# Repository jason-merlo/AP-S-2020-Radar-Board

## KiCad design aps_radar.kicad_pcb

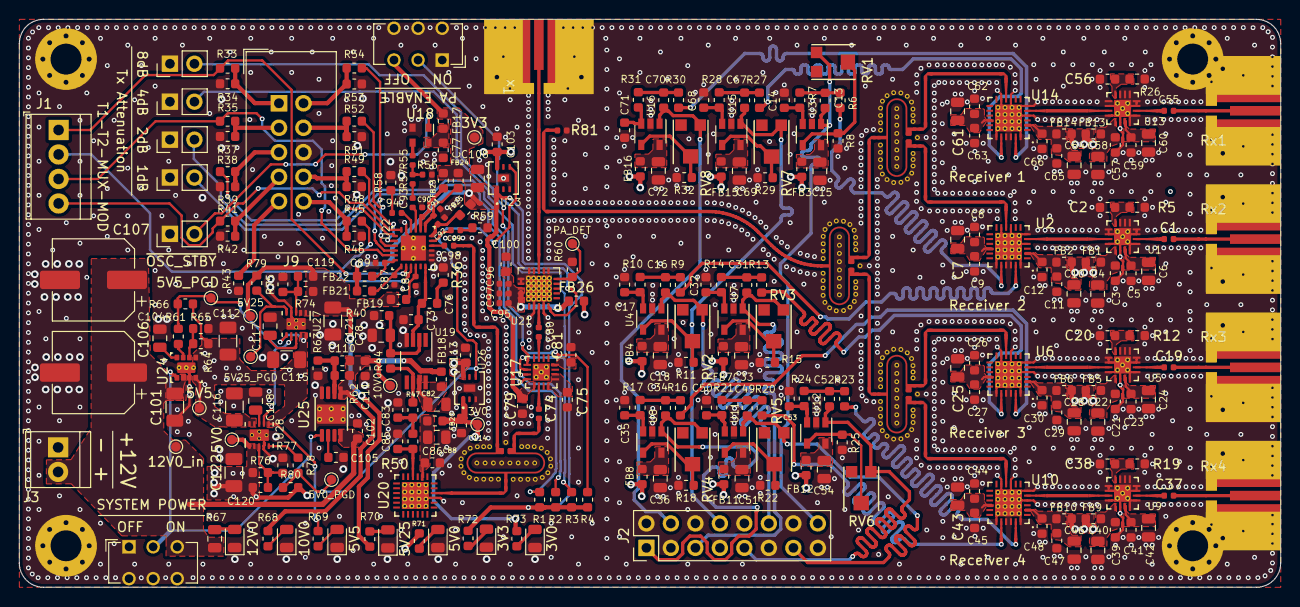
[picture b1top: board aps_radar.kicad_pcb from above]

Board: 4 copper layers, 130.8 x 58.9 mm, 360 parts (0 on the bottom side), 217 nets.

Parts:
C1, C19, C37, C55: 1.2pF; C_0402_1005Metric
C2, C20, C38, C56, C86, C105, C110, C119, C120: 10nF; C_0603_1608Metric
C3, C5, C21, C23, C39, C41, C57, C59: 1000pF; C_0603_1608Metric
C4, C6, C15, C18, C22, C24, C33, C36, C40, C42, C51, C54, C58, C60, C69, C72, C78, C82, C117, C118: 0.1uF; C_0805_2012Metric
C7, C10, C25, C28, C43, C46, C61, C64, C88, C108: 4.7uF; C_0805_2012Metric
C8, C11, C26, C29, C44, C47, C62, C65: 100pF; C_0603_1608Metric
C9, C12, C13, C14, C16, C17, C27, C30, C31, C32, C34, C35, C45, C48, C49, C50, C52, C53, C63, C66, C67, C68, C70, C71, C77: 0.01uF; C_0603_1608Metric
C73: 68pF; C_0603_1608Metric
C74, C80, C93, C94, C98, C99: 10pF; C_0402_1005Metric
C75, C81: 330pF; C_0603_1608Metric
C76: 0.68nF; C_0603_1608Metric
C79, C83: 1.8nF; C_0603_1608Metric
C84, C87, C89: 100pF; C_0402_1005Metric
C85: 0.82nF; C_0603_1608Metric
C90, C91, C92, C95, C96, C97: 0.1uF; C_0402_1005Metric
C100: 10uF; C_0603_1608Metric
C101, C112, C115, C116, C121, C122: 10uF; C_1206_3216Metric
C102, C111: 2.2uF; C_0603_1608Metric
C103, C113, C114: 1uF; C_0603_1608Metric
C104: 4.3nF; C_0805_2012Metric
C106: 68uF; CP_Elec_8x11.9
C107: DNP; CP_Elec_8x11.9
D1: 12V0; D_0805_2012Metric
D2: 10V0; D_0805_2012Metric
D3: 5V5; D_0805_2012Metric
D4: 5V25; D_0805_2012Metric
D5: 5V0; D_0805_2012Metric
D6: 3V3; D_0805_2012Metric
D7: 3V0; D_0805_2012Metric
FB1, FB2, FB3, FB4, FB5, FB6, FB7, FB8, FB9, FB10, FB11, FB12, FB13, FB14, FB15, FB16, FB17, FB18, FB20, FB26: 0; L_0603_1608Metric
FB19, FB21, FB22, FB23, FB24, FB25: 120 ohm; L_0603_1608Metric
H1, H2, H3, H4: MountingHole; MountingHole_3.2mm_M3_Pad_Via
J1: TRIG_MUX_OUT; TerminalBlock_TE_282834-4_1x04_P2.54mm_Horizontal
J2: IF_OUT; PinHeader_2x08_P2.54mm_Vertical
J3: POWER_IN; TerminalBlock_TE_282834-2_1x02_P2.54mm_Horizontal
J4: Tx; SMA_Molex_Transition
J5: Rx1; SMA_Molex_Transition
J6: Rx2; SMA_Molex_Transition
J7: Rx3; SMA_Molex_Transition
J8: Rx4; SMA_Molex_Transition
J9: LMX2491_CONN; IDC-Header_2x05_P2.54mm_Vertical
JP1: 1dB; PinHeader_1x02_P2.54mm_Vertical
JP2: 2dB; PinHeader_1x02_P2.54mm_Vertical
JP3: 4dB; PinHeader_1x02_P2.54mm_Vertical
JP4: 8dB; PinHeader_1x02_P2.54mm_Vertical
JP5: ~OSC_STBY; PinHeader_1x02_P2.54mm_Vertical
R1, R2, R3, R4, R33, R34, R35, R37, R38, R39, R41, R42, R45, R46, R48, R49, R51, R52, R53, R54, R60, R63: 10k; R_0603_1608Metric
R5, R12, R19, R26: 825; R_0603_1608Metric
R6, R7, R8, R9, R10, R11, R13, R14, R15, R16, R17, R18, R20, R21, R22, R23, R24, R25, R27, R28, R29, R30, R31, R32, R68: 499; R_0603_1608Metric
R36: 1.2k; R_0603_1608Metric
R40: 1.0k; R_0603_1608Metric
R43: DNP; R_0603_1608Metric
R44: 1.24k; R_0603_1608Metric
R47: 8.2; R_0603_1608Metric
R50: 22; R_0603_1608Metric
R55, R57: 18; R_0402_1005Metric
R56: 68; R_0402_1005Metric
R58, R59: 51; R_0603_1608Metric
R61, R78: 0; R_0603_1608Metric
R62: 86.6k; R_0603_1608Metric
R64: 590k; R_0603_1608Metric
R65, R66, R79, R80: 100k; R_0603_1608Metric
R67: 649; R_0805_2012Metric
R69: 274; R_0603_1608Metric
R70: 261; R_0603_1608Metric
R71: 249; R_0603_1608Metric
R72: 165; R_0603_1608Metric
R73: 150; R_0603_1608Metric
R74, R76: 332k; R_0603_1608Metric
R75: 59.7k; R_0603_1608Metric
R77: 63.4k; R_0603_1608Metric
R81: 50; R_0402_1005Metric
RV1, RV2, RV3, RV4, RV5, RV6, RV7, RV8: 50k; Bourns_Trimpot_TC33
SW1: PA_EN; SW_CuK_JS202011AQN_DPDT_Angled
SW2: ON/OFF; SW_CuK_JS202011AQN_DPDT_Angled
TL1: coupled_line_14db
TL2, TL3, TL4, TL5: wilkinson_3dB; wilkinson_3db
TL6, TL7, TL8, TL9, TL16, TL17, TL18, TL19, TL20, TL21, TL47, TL48, TL49, TL50, TL51, TL52, TL53, TL54, TL55, TL56, TL57, TL58: mitered_bend; mitered_bend_50
TL10, TL11, TL23, TL24, TL25, TL26, TL27, TL28, TL29, TL30, TL31, TL32, TL33, TL34, TL35, TL36, TL37, TL38, TL39, TL40, TL41, TL42, TL43, TL44, TL45, TL46: ic_taper; IC_Taper_0.22_0.35
TL12, TL13, TL14, TL15, TL22: ic_taper; IC_Taper_0.25_0.35
TP1: PA_DET; TestPoint_Pad_D1.0mm
TP2: 3V3; TestPoint_Pad_D1.0mm
TP3: 12V0_in; TestPoint_Pad_D1.0mm
TP4: 10V0; TestPoint_Pad_D1.0mm
TP5: 5V5; TestPoint_Pad_D1.0mm
TP6: 5V5_PGD; TestPoint_Pad_D1.0mm
TP7: 3V0; TestPoint_Pad_D1.0mm
TP8: 5V25; TestPoint_Pad_D1.0mm
TP9: 5V25_PGD; TestPoint_Pad_D1.0mm
TP10: 5V0; TestPoint_Pad_D1.0mm
TP11: 5V0_PGD; TestPoint_Pad_D1.0mm
U1, U5, U9, U13: HMC717A; HMC-LP3
U2, U6, U10, U14: HMC951A; HMC-LP4
U3, U4, U7, U8, U11, U12, U15, U16: OPA192; SOT-23-5
U17: HMC540S; HMC-LP3
U18: ASDMB-100MHz; Oscillator_SMD_Abracon_ASDMB-4Pin_2.5x2.0mm
U19: OPA192; VSSOP-8_3.0x3.0mm_P0.65mm
U20: HMC431; HMC-LP4
U21: TQP5523; QFN4-20-TQP5523
U22: LMX2491RTWR
U23: LP5900-TL3.3; LP5900_NGF_6
U24: TPS82140; TPS82140SILR
U25: TPS7A49; TPS7A4901_DGN_8
U26: LP5900-TL3.0; LP5900_NGF_6
U27: TPS7A90; TPS7A9xDSKR
U28: TPS7A92; TPS7A9xDSKR

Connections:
+3V0: C114.1, FB20.2, R73.2, TP7.1, U26.1
+3V3: C79.1, C108.1, FB17.1, FB21.2, FB22.2, FB23.2, FB24.2, FB25.2, R1.1, R2.1, R3.1, R4.1, R72.2, SW1.3, TP2.1, U17.1, U23.1
+5V: C103.1, C113.1, C120.1, C122.1, FB1.1, FB2.1, FB3.1, FB4.1, FB5.1, FB6.1, FB7.1, FB8.1, FB9.1, FB10.1, FB11.1, FB12.1, FB13.1, FB14.1, FB15.1, FB16.1, FB26.2, R71.2, R76.1, R80.1, TP10.1, U23.6, U26.6, U28.1, U28.2
+5V25: C119.1, C121.1, FB19.2, R70.2, R74.1, R79.1, TP8.1, U27.1, U27.2
+10V: C110.1, C111.1, FB18.2, R62.1, R68.2, TP4.1, U25.1
/LMX_MOD: J1.4, R41.2, U22.12
/LMX_MUXOUT: J1.3, R35.2, U22.17
/LMX_TRIG1: J1.1, R33.2, U22.20
/LMX_TRIG2: J1.2, R45.2, U22.21
/RX1_I: C70.1, J2.4, RV8.1, U16.1
/RX1_Q: C67.1, J2.8, RV7.1, U15.1
/RX2_I: C16.1, J2.12, RV2.1, U4.1
/RX2_Q: C13.1, J2.16, RV1.1, U3.1
/RX3_I: C34.1, J2.1, RV4.1, U8.1
/RX3_Q: C31.1, J2.5, RV3.1, U7.1
/RX4_I: C52.1, J2.9, RV6.1, U12.1
/RX4_Q: C49.1, J2.13, RV5.1, U11.1
/power/5V0_PGD: R78.1, R80.2, TP11.1, U23.4, U26.4
/power/5V5_OUT: C112.1, C115.1, C116.1, R64.1, R66.1, R69.2, TP5.1, U24.4, U24.5, U27.6, U27.9, U27.10, U28.6, U28.9, U28.10
/power/5V5_PGD: R61.1, R66.2, TP6.1, U27.7, U28.7
/power/5V25_PGD: R79.2, TP9.1, U27.5
/power/+12V0_IN_CONN: C101.1, C102.1, C106.1, C107.1, J3.2, R67.2, SW2.3, TP3.1, U24.2, U25.8
/power/POWER_SW: SW2.2, U24.1, U25.5
/receiver_1/ANT_IN: C55.2, J5.1
/receiver_1/IF1_RAW: R30.2, TL45.2
/receiver_1/IF2_RAW: R27.2, TL46.2
/receiver_1/LNA_OUT: TL32.2, TL36.2
/receiver_2/ANT_IN: C1.2, J6.1
/receiver_2/IF1_RAW: R9.2, TL24.2
/receiver_2/IF2_RAW: R6.2, TL37.2
/receiver_2/LNA_OUT: TL29.2, TL33.2
/receiver_3/ANT_IN: C19.2, J7.1
/receiver_3/IF1_RAW: R16.2, TL39.2
/receiver_3/IF2_RAW: R13.2, TL40.2
/receiver_3/LNA_OUT: TL30.2, TL34.2
/receiver_4/ANT_IN: C37.2, J8.1
/receiver_4/IF1_RAW: R23.2, TL42.2
/receiver_4/IF2_RAW: R20.2, TL43.2
/receiver_4/LNA_OUT: TL31.2, TL35.2
/transmitter/ATTEN_OUT: C80.2, TL14.2
/transmitter/LMX_CE: R38.2, U22.13
/transmitter/LMX_CLK: R49.2, U22.14
/transmitter/LMX_CPOUT: C73.1, C76.1, TL22.2, U19.3
/transmitter/LMX_DATA: R52.2, U22.15
/transmitter/LMX_FIN: C98.1, TL19.1
/transmitter/LMX_LE: R54.2, U22.16
/transmitter/LMX_VCP: C84.1, FB19.1, U22.22
/transmitter/LO_1: TL50.1, TL55.2
/transmitter/LO_2: TL47.1, TL57.1
/transmitter/LO_3: TL48.1, TL56.2
/transmitter/LO_4: TL49.1, TL58.1
/transmitter/PA_OUT: TL1.1, TL15.2
/transmitter/REF_OUT: R55.2, U18.3
/transmitter/TX_OUT: J4.1, TL1.2
/transmitter/VCO_OUT: C74.1, TL21.1
/~ATTEN_1DB: JP1.2, R1.2, U17.16
/~ATTEN_2DB: JP2.2, R2.2, U17.15
/~ATTEN_4DB: JP3.2, R3.2, U17.14
/~ATTEN_8DB: JP4.2, R4.2, U17.13
GND: C2.2, C3.2, C4.2, C5.2, C6.2, C7.2, C8.1, C9.1, C10.2, C11.1, C12.1, C14.2, C15.2, C17.2, C18.2, C20.2, C21.2, C22.2, C23.2, C24.2, C25.2, C26.1, C27.1, C28.2, C29.1, C30.1, C32.2, C33.2, C35.2, C36.2, C38.2, C39.2, C40.2, C41.2, C42.2, C43.2, C44.1, C45.1, C46.2, C47.1, C48.1, C50.2, C51.2, C53.2, C54.2, C56.2, C57.2, C58.2, C59.2, C60.2, C61.2, C62.1, C63.1, C64.2, C65.1, C66.1, C68.2, C69.2, C71.2, C72.2, C73.2, C75.1, C77.2, C78.2, C79.2, C81.2, C82.2, C83.2, C84.2, C85.2, C86.2, C87.2, C88.2, C89.2, C90.2, C91.2, C92.2, C95.2, C96.2, C97.2, C100.2, C101.2, C102.2, C103.2, C104.2, C105.2, C106.2, C107.2, C108.2, C111.2, C112.2, C113.2, C114.2, C115.2, C116.2, C117.2, C118.2, C121.2, C122.2, D1.1, D2.1, D3.1, D4.1, D5.1, D6.1, D7.1, H1.1, H2.1, H3.1, H4.1, J2.2, J2.3, J2.6, J2.7, J2.10, J2.11, J2.14, J2.15, J3.1, J4.2, J5.2, J6.2, J7.2, J8.2, J9.6, JP1.1, JP2.1, JP3.1, JP4.1, JP5.1, R5.1, R8.2, R11.2, R12.1, R15.2, R18.2, R19.1, R22.2, R25.2, R26.1, R29.2, R32.2, R34.1, R36.2, R37.1, R39.1, R40.2, R42.1, R43.1, R46.1, R48.1, R51.1, R53.1, R56.2, R58.1, R59.1, R60.2, R63.2, R65.2, R75.2, R77.2, R81.2, SW1.1, SW1.4, SW1.5, SW1.6, SW2.1, SW2.4, SW2.5, SW2.6, TL2.5, TL3.5, TL4.5, TL5.5, U1.1, U1.3, U1.4, U1.5, U1.6, U1.7, U1.9, U1.10, U1.12, U1.14, U1.16, U1.17, U2.4, U2.6, U2.9, U2.11, U2.19, U2.21, U2.22, U2.24, U2.25, U3.2, U4.2, U5.1, U5.3, U5.4, U5.5, U5.6, U5.7, U5.9, U5.10, U5.12, U5.14, U5.16, U5.17, U6.4, U6.6, U6.9, U6.11, U6.19, U6.21, U6.22, U6.24, U6.25, U7.2, U8.2, U9.1, U9.3, U9.4, U9.5, U9.6, U9.7, U9.9, U9.10, U9.12, U9.14, U9.16, U9.17, U10.4, U10.6, U10.9, U10.11, U10.19, U10.21, U10.22, U10.24, U10.25, U11.2, U12.2, U13.1, U13.3, U13.4, U13.5, U13.6, U13.7, U13.9, U13.10, U13.12, U13.14, U13.16, U13.17, U14.4, U14.6, U14.9, U14.11, U14.19, U14.21, U14.22, U14.24, U14.25, U15.2, U16.2, U17.17, U18.2, U19.4, U20.15, U20.25, U21.2, U21.4, U21.11, U21.12, U21.14, U21.15, U21.16, U21.17, U21.21, U22.1, U22.2, U22.3, U22.11, U22.25, U23.3, U23.7, U24.3, U24.9, U25.4, U25.9, U26.3, U26.7, U27.4, U27.11, U28.4, U28.11
unnamed: C1.1, TL25.2
unnamed: C2.1, R5.2, U1.8
unnamed: C3.1, C4.1, C5.1, C6.1, FB1.2, U1.13, U1.15
unnamed: C7.1, C8.2, C9.2, C10.1, C11.2, C12.2, FB2.2, U2.2, U2.16
unnamed: C13.2, R6.1, R7.2
unnamed: C14.1, R7.1, U3.3
unnamed: C15.1, FB3.2, U3.5
unnamed: C16.2, R9.1, R10.2
unnamed: C17.1, R10.1, U4.3
unnamed: C18.1, FB4.2, U4.5
unnamed: C19.1, TL26.2
unnamed: C20.1, R12.2, U5.8
unnamed: C21.1, C22.1, C23.1, C24.1, FB5.2, U5.13, U5.15
unnamed: C25.1, C26.2, C27.2, C28.1, C29.2, C30.2, FB6.2, U6.2, U6.16
unnamed: C31.2, R13.1, R14.2
unnamed: C32.1, R14.1, U7.3
unnamed: C33.1, FB7.2, U7.5
unnamed: C34.2, R16.1, R17.2
unnamed: C35.1, R17.1, U8.3
unnamed: C36.1, FB8.2, U8.5
unnamed: C37.1, TL27.2
unnamed: C38.1, R19.2, U9.8
unnamed: C39.1, C40.1, C41.1, C42.1, FB9.2, U9.13, U9.15
unnamed: C43.1, C44.2, C45.2, C46.1, C47.2, C48.2, FB10.2, U10.2, U10.16
unnamed: C49.2, R20.1, R21.2
unnamed: C50.1, R21.1, U11.3
unnamed: C51.1, FB11.2, U11.5
unnamed: C52.2, R23.1, R24.2
unnamed: C53.1, R24.1, U12.3
unnamed: C54.1, FB12.2, U12.5
unnamed: C55.1, TL28.2
unnamed: C56.1, R26.2, U13.8
unnamed: C57.1, C58.1, C59.1, C60.1, FB13.2, U13.13, U13.15
unnamed: C61.1, C62.2, C63.2, C64.1, C65.2, C66.2, FB14.2, U14.2, U14.16
unnamed: C67.2, R27.1, R28.2
unnamed: C68.1, R28.1, U15.3
unnamed: C69.1, FB15.2, U15.5
unnamed: C70.2, R30.1, R31.2
unnamed: C71.1, R31.1, U16.3
unnamed: C72.1, FB16.2, U16.5
unnamed: C74.2, TL10.2
unnamed: C75.2, U17.4, U17.5, U17.6
unnamed: C76.2, R36.1
unnamed: C77.1, FB17.2, U18.4
unnamed: C78.1, R40.1, R44.2, U19.2
unnamed: C80.1, TL11.2
unnamed: C81.1, U17.8
unnamed: C82.1, FB18.1, U19.7
unnamed: C83.1, R47.1, R50.2
unnamed: C85.1, R50.1, TL12.2
unnamed: C86.1, C88.1, FB20.1, U20.20
unnamed: C93.1, U22.9
unnamed: C93.2, R57.1
unnamed: C94.1, U22.10
unnamed: C94.2, R58.2
unnamed: C98.2, U22.4
unnamed: C99.1, R59.2
unnamed: C99.2, U22.5
unnamed: C95.1, C96.1, C97.1, C100.1, FB26.1, U21.18, U21.19, U21.20
unnamed: C104.1, U24.8
unnamed: C105.1, U25.6
unnamed: C110.2, R62.2, R63.1, U25.2
unnamed: C117.1, U27.8
unnamed: C118.1, U28.8
unnamed: C119.2, R74.2, R75.1, U27.3
unnamed: C120.2, R76.2, R77.1, U28.3
unnamed: D1.2, R67.1
unnamed: D2.2, R68.1
unnamed: D3.2, R69.1
unnamed: D4.2, R70.1
unnamed: D5.2, R71.1
unnamed: D6.2, R72.1
unnamed: D7.2, R73.1
unnamed: J9.1, R33.1, R34.2
unnamed: J9.2, R53.2, R54.1
unnamed: J9.3, R35.1, R37.2
unnamed: J9.4, R51.2, R52.1
unnamed: J9.5, R38.1, R39.2
unnamed: J9.7, R41.1, R42.2
unnamed: J9.8, R48.2, R49.1
unnamed: J9.9, R43.2
unnamed: J9.10, R45.1, R46.2
unnamed: JP5.2, U18.1
unnamed: R8.1, RV1.2, U3.4
unnamed: R11.1, RV2.2, U4.4
unnamed: R15.1, RV3.2, U7.4
unnamed: R18.1, RV4.2, U8.4
unnamed: R22.1, RV5.2, U11.4
unnamed: R25.1, RV6.2, U12.4
unnamed: R29.1, RV7.2, U15.4
unnamed: R32.1, RV8.2, U16.4
unnamed: R44.1, R47.2, U19.6
unnamed: R55.1, R56.1, R57.2
unnamed: R60.1, TP1.1, U21.10
unnamed: R61.2, U24.7
unnamed: R64.2, R65.1, U24.6
unnamed: R78.2, U28.5
unnamed: R81.1, TL1.3
unnamed: SW1.2, U21.5
unnamed: TL1.4, TL2.1
unnamed: TL2.2, TL8.2
unnamed: TL2.3, TL6.1
unnamed: TL3.1, TL7.2
unnamed: TL3.2, TL53.2
unnamed: TL3.3, TL51.1
unnamed: TL4.1, TL9.1
unnamed: TL4.2, TL54.2
unnamed: TL4.3, TL52.1
unnamed: TL6.2, TL9.2
unnamed: TL7.1, TL8.1
unnamed: TL10.1, U17.2
unnamed: TL11.1, U17.11
unnamed: TL12.1, U20.22
unnamed: TL13.1, U20.16
unnamed: TL13.2, TL16.2
unnamed: TL14.1, U21.3
unnamed: TL15.1, U21.13
unnamed: TL5.1, TL16.1
unnamed: TL17.1, TL18.1
unnamed: TL5.2, TL17.2
unnamed: TL18.2, TL19.2
unnamed: TL5.3, TL20.1
unnamed: TL20.2, TL21.2
unnamed: TL22.1, U22.24
unnamed: TL23.1, U2.10
unnamed: TL23.2, TL47.2
unnamed: TL24.1, U2.23
unnamed: TL25.1, U1.2
unnamed: TL26.1, U5.2
unnamed: TL27.1, U9.2
unnamed: TL28.1, U13.2
unnamed: TL29.1, U1.11
unnamed: TL30.1, U5.11
unnamed: TL31.1, U9.11
unnamed: TL32.1, U13.11
unnamed: TL33.1, U2.5
unnamed: TL34.1, U6.5
unnamed: TL35.1, U10.5
unnamed: TL36.1, U14.5
unnamed: TL37.1, U2.20
unnamed: TL38.1, U6.10
unnamed: TL38.2, TL48.2
unnamed: TL39.1, U6.23
unnamed: TL40.1, U6.20
unnamed: TL41.1, U10.10
unnamed: TL41.2, TL49.2
unnamed: TL42.1, U10.23
unnamed: TL43.1, U10.20
unnamed: TL44.1, U14.10
unnamed: TL44.2, TL50.2
unnamed: TL45.1, U14.23
unnamed: TL46.1, U14.20
unnamed: TL51.2, TL57.2
unnamed: TL52.2, TL58.2
unnamed: TL53.1, TL55.1
unnamed: TL54.1, TL56.1
VCC: C87.1, C89.1, C90.1, C91.1, C92.1, FB21.1, FB22.1, FB23.1, FB24.1, FB25.1, U22.6, U22.7, U22.8, U22.18, U22.19

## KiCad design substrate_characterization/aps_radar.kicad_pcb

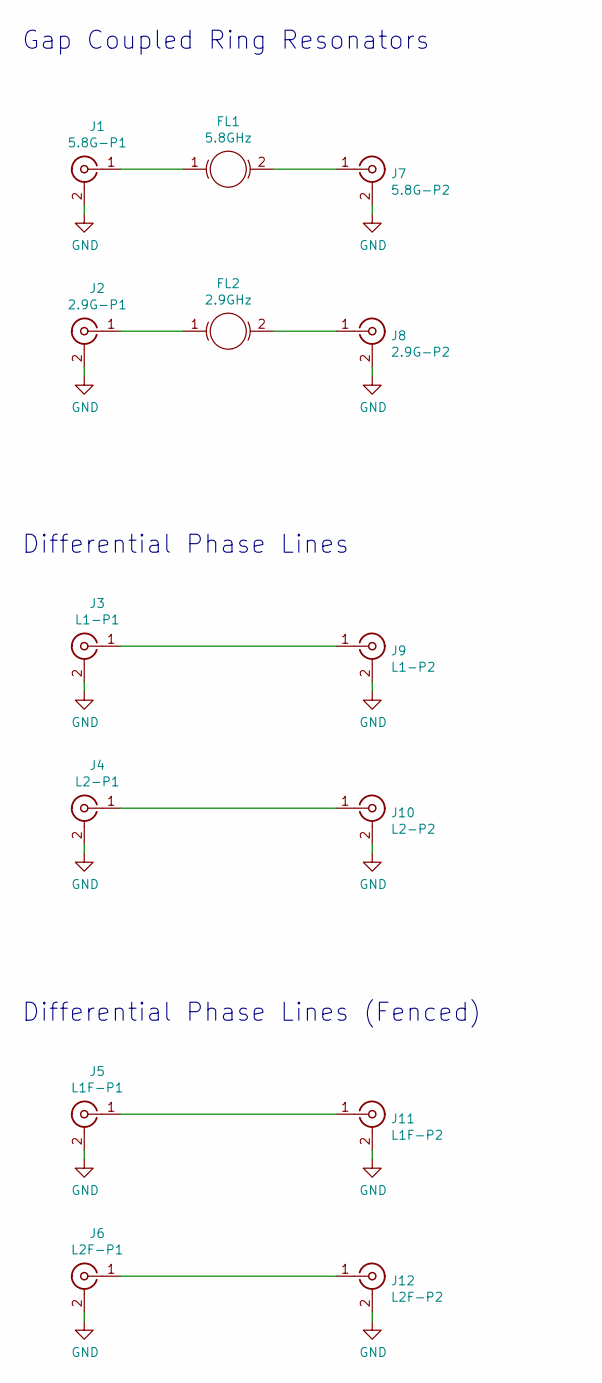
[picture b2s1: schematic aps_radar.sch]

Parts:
FL1: 5.8GHz; 5.8G_ring_resonator_2mm
FL2: 2.9GHz; 2.9G_ring_resonator_2mm
J1: 5.8G-P1; SMA_Molex_73251-1153_EdgeMount_Horizontal
J2: 2.9G-P1; SMA_Molex_73251-1153_EdgeMount_Horizontal
J3: L1-P1; SMA_Molex_73251-1153_EdgeMount_Horizontal
J4: L2-P1; SMA_Molex_73251-1153_EdgeMount_Horizontal
J5: L1F-P1; SMA_Molex_73251-1153_EdgeMount_Horizontal
J6: L2F-P1; SMA_Molex_73251-1153_EdgeMount_Horizontal
J7: 5.8G-P2; SMA_Molex_73251-1153_EdgeMount_Horizontal
J8: 2.9G-P2; SMA_Molex_73251-1153_EdgeMount_Horizontal
J9: L1-P2; SMA_Molex_73251-1153_EdgeMount_Horizontal
J10: L2-P2; SMA_Molex_73251-1153_EdgeMount_Horizontal
J11: L1F-P2; SMA_Molex_73251-1153_EdgeMount_Horizontal
J12: L2F-P2; SMA_Molex_73251-1153_EdgeMount_Horizontal

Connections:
GND: J1.2 (Ext), J2.2 (Ext), J3.2 (Ext), J4.2 (Ext), J5.2 (Ext), J6.2 (Ext), J7.2 (Ext), J8.2 (Ext), J9.2 (Ext), J10.2 (Ext), J11.2 (Ext), J12.2 (Ext)
unnamed: FL1.1, J1.1 (In)
unnamed: FL1.2, J7.1 (In)
unnamed: FL2.1, J2.1 (In)
unnamed: FL2.2, J8.1 (In)
unnamed: J3.1 (In), J9.1 (In)
unnamed: J4.1 (In), J10.1 (In)
unnamed: J5.1 (In), J11.1 (In)
unnamed: J6.1 (In), J12.1 (In)

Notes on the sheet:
Gap Coupled Ring Resonators
Differential Phase Lines
Differential Phase Lines (Fenced)

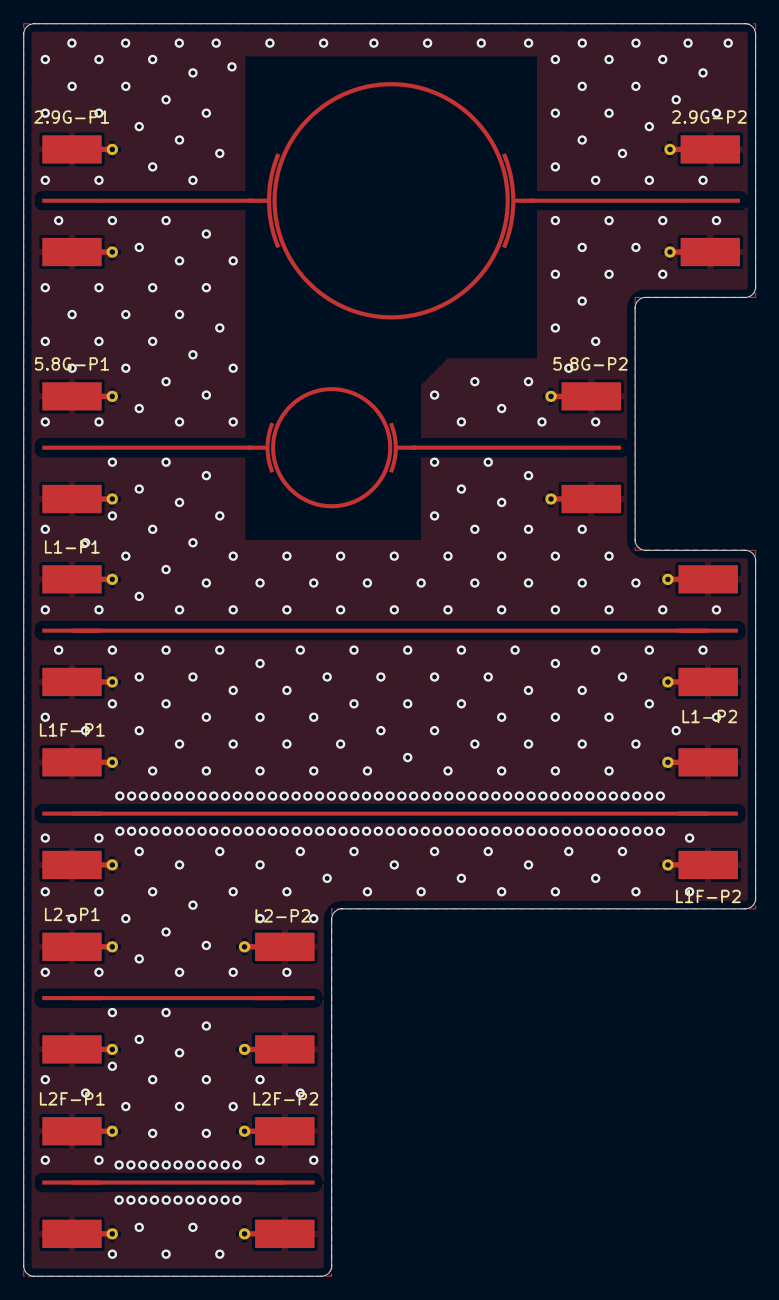
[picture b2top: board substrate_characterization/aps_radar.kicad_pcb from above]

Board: 4 copper layers, 62.5 x 106.9 mm, 14 parts (0 on the bottom side), 9 nets.

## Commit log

2020-01-31 Added gitignore file
2020-02-06 Initial library commit
2020-02-06 Added substrate characteriztion board
2020-02-06 I added footprint and schematic for hmc951a
2020-02-06 added substrate characterization board
2020-02-06 Added radar project
2020-02-07 Updated footprints, added LNA
2020-02-07 added HCP_16_3 footprint
2020-02-07 added footprint and schematic for bpf
2020-02-07 Added tracking for footprint library
2020-02-07 added more
2020-02-07 Removed duplicate footprint, cleaned up footprints
2020-02-11 Added LMX2491 to library
2020-02-11 Began transmitter layout
2020-02-12 Added a capacitor to schem
2020-02-18 receiver
2020-02-18 added sym_lib_table
2020-02-21 Added transmitter components
2020-02-26 updated SMA footprint, added splitter symbol
2020-02-26 Added footprints for couplers
2020-02-26 Updated sma footprint
2020-02-26 Added .DS_Store to .gitignore
2020-02-26 Renamed substrate characterization board to avoid confusion
2020-03-02 Finished schematic for transmitter
2020-03-02 Added transmitter.sch
2020-03-02 Integrated transmitter and receiver. Need to add ferrite beads and power supply module.
2020-03-02 Removed library from repo; created new repository for library to avoid conflicts.
2020-03-02 Moved substrate characterization board to its own repo.
2020-03-02 Updated gitignore and folder structure
2020-03-02 Updated library file paths to relative path variable
2020-03-04 Finished power schematic and main page
2020-03-05 Addressed all TODOs
2020-03-06 Started footprint association
2020-03-07 Assigned components to each part
2020-03-07 Updated potentiometer footprint, started layout
2020-03-09 Spec'd new components for some parts, bfinished transmitter layout.
2020-03-09 Layout updates
2020-03-10 Finished placing transmitter and power
2020-03-10 Began receiver layout
2020-03-11 Finished placing parts
2020-03-11 Updated .gitignore to ignore log files
2020-03-12 Finished layout
2020-03-13 Added SMA model
2020-03-13 Added generated files to .gitignore

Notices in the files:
parts and their libraries:
Copyright 2016 Accelerated Designs. All rights reserved.
